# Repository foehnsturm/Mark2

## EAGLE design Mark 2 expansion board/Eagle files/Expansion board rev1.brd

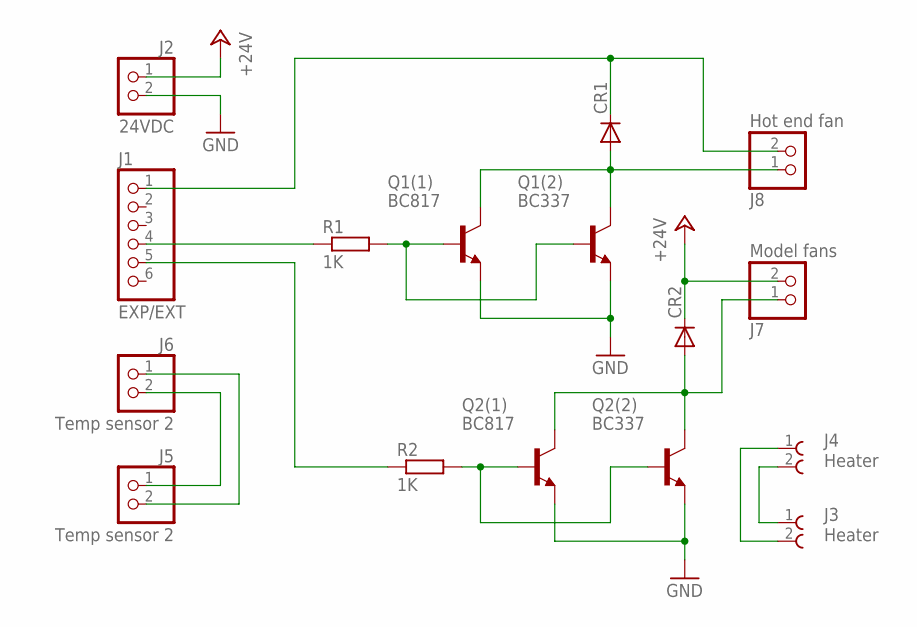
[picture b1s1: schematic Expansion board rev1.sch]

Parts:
CR1, CR2: TESTDIODE; DO214AC
J1: EXP/EXT; 2X03
J2: 24VDC; 1X02
J3, J4: Heater; 691216710002
J5, J6: Temp sensor 2; 1X02
J7: Model fans; 1X02
J8: Hot end fan; JST_XH_2_RA
Q1(1), Q2(1): BC817; SOT23-BEC
Q1(2), Q2(2): BC337; TO92
R1, R2: 1K; M3216

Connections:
+24V: CR2.C, J2.1, J7.2
GND: J2.2, Q1(1).E, Q1(2).1 (E), Q2(1).E, Q2(2).1 (E)
unnamed: CR2.A, J7.1, Q2(1).C, Q2(2).3 (C)
unnamed: J3.2, J4.1
unnamed: CR1.A, J8.1, Q1(1).C, Q1(2).3 (C)
unnamed: J3.1, J4.2
unnamed: Q2(1).B, Q2(2).2 (B), R2.2
unnamed: Q1(1).B, Q1(2).2 (B), R1.2
unnamed: CR1.C, J1.1, J8.2
unnamed: J1.5, R2.1
unnamed: J1.4, R1.1
unnamed: J5.1, J6.2
unnamed: J5.2, J6.1

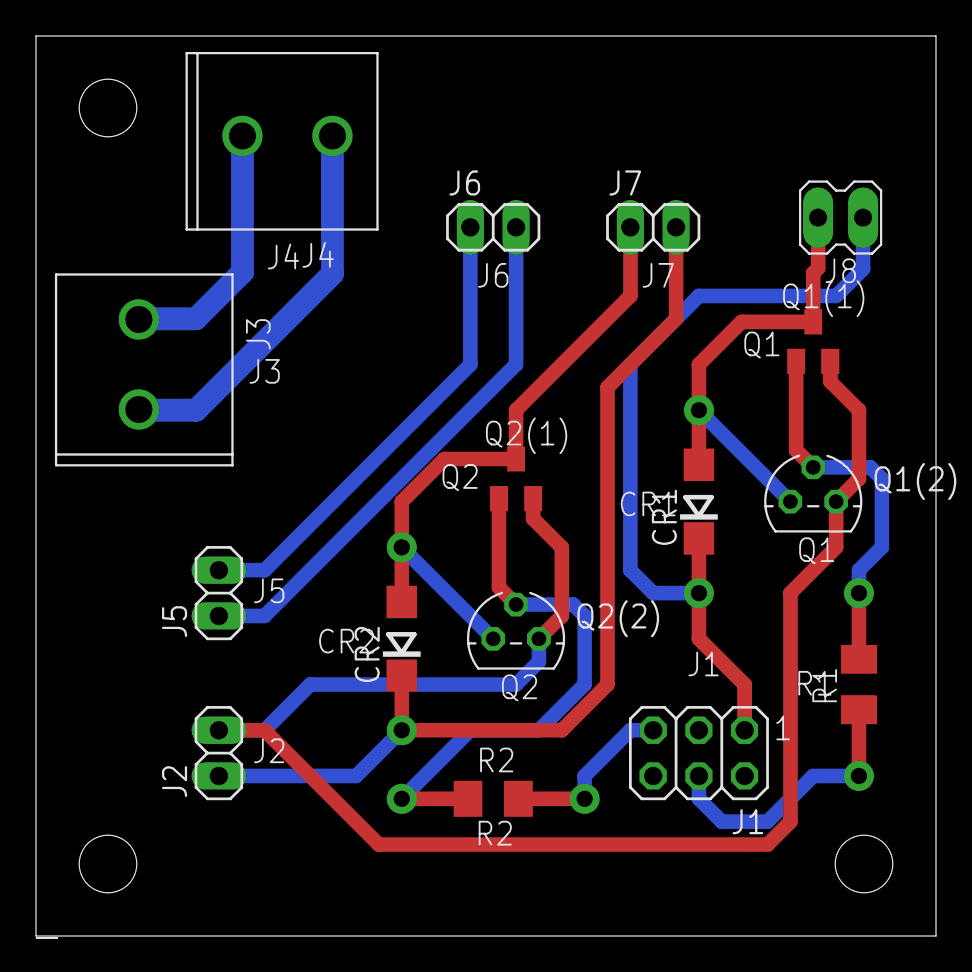
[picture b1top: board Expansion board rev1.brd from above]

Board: 2 copper layers, 50.0 x 50.0 mm, 16 parts (0 on the bottom side), 13 nets.

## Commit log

2017-03-07 Create foo
2017-03-07 Rename cura-definitions/ultimaker2_extruder1.def.json to cura-definitions/extruders/ultimaker2_extruder1.def.json
2017-03-07 Rename cura-definitions/ultimaker2_extruder2.def.json to cura-definitions/extruders/ultimaker2_extruder2.def.json
2017-03-07 Rename cura-definitions/ultimaker2_mark2.def.json to cura-definitions/definitions/ultimaker2_mark2.def.json
2017-03-07 Rename cura-definitions/ultimaker2_mark2_0.25.inst.cfg to cura-definitions/variants/ultimaker2_mark2_0.25.inst.cfg
2017-03-07 Rename cura-definitions/ultimaker2_mark2_0.4.inst.cfg to cura-definitions/variants/ultimaker2_mark2_0.4.inst.cfg
2017-03-07 Rename cura-definitions/ultimaker2_mark2_0.6.inst.cfg to cura-resources/variants/ultimaker2_mark2_0.6.inst.cfg
2017-03-07 Rename cura-definitions/definitions/ultimaker2_mark2.def.json to cura-resources/definitions/ultimaker2_mark2.def.json
2017-03-07 Rename cura-definitions/extruders/ultimaker2_extruder1.def.json to cura-resources/extruders/ultimaker2_extruder1.def.json
2017-03-07 Rename cura-definitions/extruders/ultimaker2_extruder2.def.json to cura-resources/extruders/ultimaker2_extruder2.def.json
2017-03-07 Rename cura-definitions/variants/ultimaker2_mark2_0.25.inst.cfg to cura-resources/variants/ultimaker2_mark2_0.25.inst.cfg
2017-03-07 Rename cura-definitions/variants/ultimaker2_mark2_0.4.inst.cfg to cura-resources/variants/ultimaker2_mark2_0.4.inst.cfg
2017-03-07 Rename cura-definitions/ultimaker2_mark2_0.8.inst.cfg to cura-resources/variants/ultimaker2_mark2_0.8.inst.cfg
2017-03-07 Rename cura-definitions/README.md to cura-resources/README.md
2017-03-26 Added modified dock wedge for use with flexible filament.
    This should improve grip and reduce the risk of over tightening.
2017-04-14 add part-files for feeder-mount
2017-04-14 add firmware hex-files V17.02.2
2017-04-17 add part-files for the (optional) cable-clamp
2017-04-18 Coupling with slightly changed pockets for the magnets. Split head stl in two files because only one needs support
2017-04-18 removed coupling rc1 files
2017-04-18 Added Cura postprocessing script for removing unnecessary moves
2017-04-25 add files for xy-calibration
2017-04-28 added tese stick dock and adjustable feeder mount
2017-05-02 added BOM
2017-05-02 changed length of print hread screws
2017-05-02 renamed BOM
2017-05-03 renaming for consistent file names
2017-05-03 BOM change
    Because it's likely nobody wants a reel of 150+ diodes
2017-05-04 Add files via upload
    Added expansion board carrier + clamps
2017-05-05 updated Cura definition files
2017-05-23 Add setting_version required for Cura 2.6
2017-06-01 changed initital priming position for ext from Y20 to Y25
2017-07-14 firmware update V17.06: round extruder offsets to a multiple of a step
2017-08-04 disable "start_layers_at_same_position"
2017-08-21 bugfix: add "G92 E0" at the end of the start script (CuraEngine always assumes E coord == 0 at the beginning of a print)
2017-10-07 add Tinker-Mark2 firmware V17.09
2018-01-26 Corrected hole depth for the magnets
    Holes in the print head now 2 mm deep instead of 2.4 mm. Coupling plate now 3.75 mm instead of 3.95 mm. Now there should be a gap of 0.25 mm between both parts when the magnets are inserted.
2018-02-07 Eliminated 0.25 mm z offset of both parts
2018-02-17 - remove the link to the UM2+ quality profiles - adjust start script for Cura 3.2
2019-03-10 firmware V19.03.1 - fix a bug in power budget when build plate is in bang-bang mode - add material load function to the MOVE menu

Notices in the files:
parts and their libraries:
Wurth_EAGLE-TERMINAL_BLOCKS-rev16e: Copyright: Würth Elektronik
